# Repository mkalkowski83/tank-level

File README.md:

# Tank Level Sensor / Czujnik poziomu tanku

| Language | Documentation |
|----------|----------------|
| **English** | [README.en.md](README.en.md) |
| **Polski** | [README.pl.md](README.pl.md) |

Firmware (language-neutral): [`esphome/tank-level-sensor.yaml`](esphome/tank-level-sensor.yaml)

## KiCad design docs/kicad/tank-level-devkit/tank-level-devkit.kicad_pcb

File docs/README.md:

# Documentation / Dokumentacja

## Schematics / Schematy

| Topic | English | Polski |
|-------|---------|--------|
| Wiring diagram | [wiring-diagram.en.md](schematics/wiring-diagram.en.md) | [wiring-diagram.pl.md](schematics/wiring-diagram.pl.md) |
| DevKit connections | [connections-devkit.en.md](schematics/connections-devkit.en.md) | [connections-devkit.pl.md](schematics/connections-devkit.pl.md) |
| DevKit + AO3401A (active) | [connections-ao3401a.en.md](schematics/connections-ao3401a.en.md) | [connections-ao3401a.pl.md](schematics/connections-ao3401a.pl.md) |
| FireBeetle (target) | [connections-firebeetle.en.md](schematics/connections-firebeetle.en.md) | [connections-firebeetle.pl.md](schematics/connections-firebeetle.pl.md) |
| Schematic (KiCad PDF) | [tank-level-devkit.pdf](schematics/tank-level-devkit.pdf) | [tank-level-devkit.pdf](schematics/tank-level-devkit.pdf) |

## KiCad / KiCad

| Topic | Project |
|-------|---------|
| DevKit + AO3401A schematic | [tank-level-devkit.kicad_pro](kicad/tank-level-devkit/tank-level-devkit.kicad_pro) — [README.pl.md](kicad/tank-level-devkit/README.pl.md) |

## Design & plan / Specyfikacja i plan

| Document | English | Polski |
|----------|---------|--------|
| Design spec | [design.en.md](superpowers/specs/2026-08-25-tank-level-sensor-design.en.md) | [design.pl.md](superpowers/specs/2026-08-25-tank-level-sensor-design.pl.md) |
| AO3401A migration | [ao3401a-migration.en.md](superpowers/specs/2026-09-02-ao3401a-migration-design.en.md) | [ao3401a-migration.pl.md](superpowers/specs/2026-09-02-ao3401a-migration-design.pl.md) |
| AO3401A implementation plan | [ao3401a-plan.en.md](superpowers/plans/2026-09-02-ao3401a-migration.en.md) | [ao3401a-plan.pl.md](superpowers/plans/2026-09-02-ao3401a-migration.pl.md) |
| Implementation plan | [plan.en.md](superpowers/plans/2026-08-25-tank-level-sensor.en.md) | [plan.pl.md](superpowers/plans/2026-08-25-tank-level-sensor.pl.md) |

## Firmware / Firmware

| Document | English | Polski |
|----------|---------|--------|
| ESPHome guide | [README.en.md](../esphome/README.en.md) | [README.pl.md](../esphome/README.pl.md) |

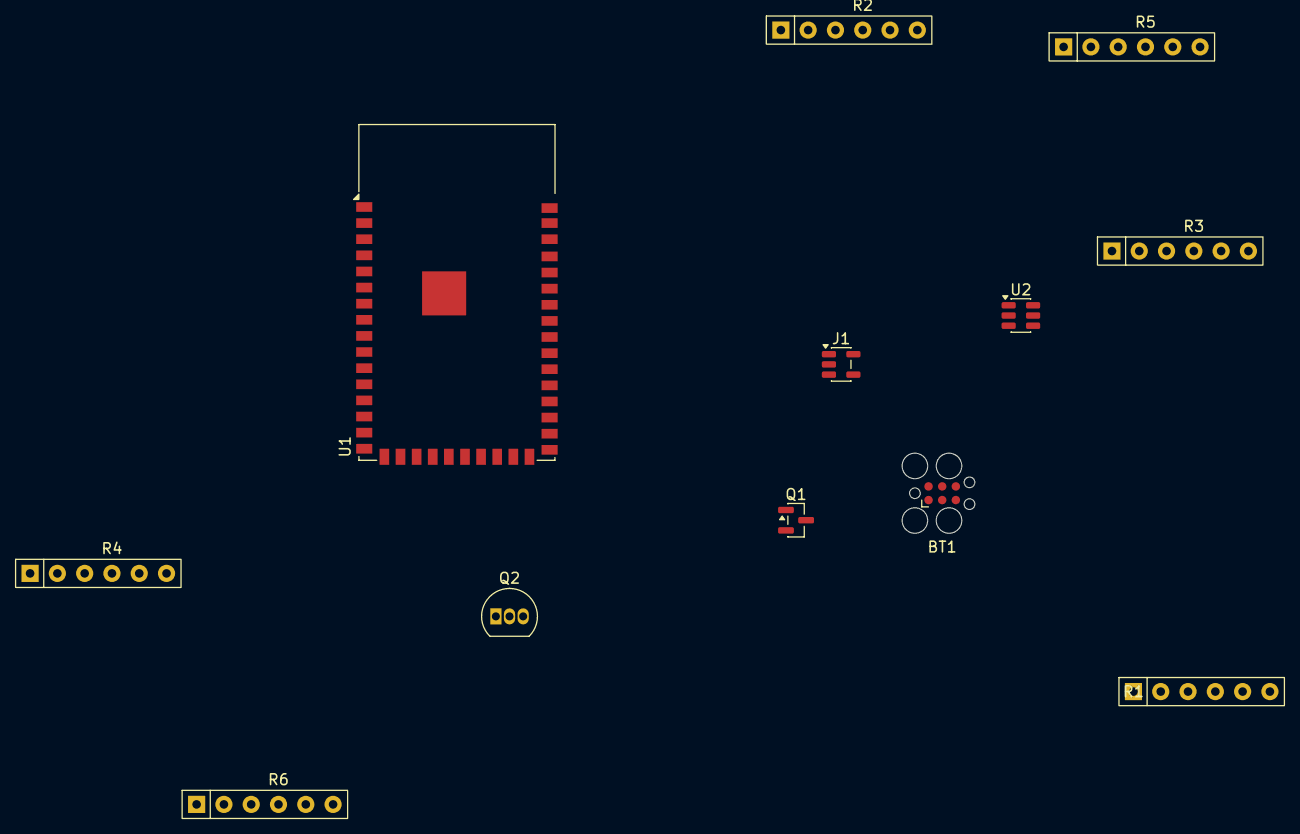
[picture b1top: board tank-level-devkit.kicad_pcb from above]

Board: 2 copper layers, 12 parts (0 on the bottom side), 11 nets, no tracks yet.

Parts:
BT1: 18650; Tag-Connect_TC2030-IDC-FP_2x03_P1.27mm_Vertical
J1: JSN-SR04T; SOT-23-5
Q1: AO3401A; SOT-23
Q2: 2N3904; TO-92_Inline
R1, R2, R3: 10K; R_Array_SIP6
R4: 20K; R_Array_SIP6
R5, R6: 100K; R_Array_SIP6
U1: ESP32_DevKit_V1; ESP32-S2-WROVER
U2: MT3608; SOT-23-6

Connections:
unnamed: J1.4 (ECHO), R3.2
unnamed: J1.2 (GND), Q2.1 (E), R4.1, R6.2, U1.2 (GND), U2.2 (IN-), U2.4 (OUT-)
unnamed: J1.3 (TRIG), U1.4 (GPIO25/TRIG)
unnamed: J1.1 (VCC), Q1.3 (D)
unnamed: Q1.1 (G), R1.1
unnamed: Q1.2 (S), Q2.3 (C), R1.2, U1.1 (5V/VIN), U2.3 (OUT+)
unnamed: Q2.2 (B), R2.1
unnamed: R2.2, U1.3 (GPIO4)
unnamed: R3.1, R4.2, U1.5 (GPIO26/ECHO)
unnamed: R5.2, R6.1, U1.6 (GPIO34/ADC)
unnamed: R5.1, U2.1 (IN+)

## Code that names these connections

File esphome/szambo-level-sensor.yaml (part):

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  ultrasonic_pulse_time: 20us
  reject_short_echo: "true"
  log_level: INFO
  pin_sensor_power: GPIO4
  pin_ultrasonic_trig: GPIO25
  pin_ultrasonic_echo: GPIO26
  pin_wakeup: GPIO33
  pin_battery_adc: GPIO34

globals:
  - id: boot_count
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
